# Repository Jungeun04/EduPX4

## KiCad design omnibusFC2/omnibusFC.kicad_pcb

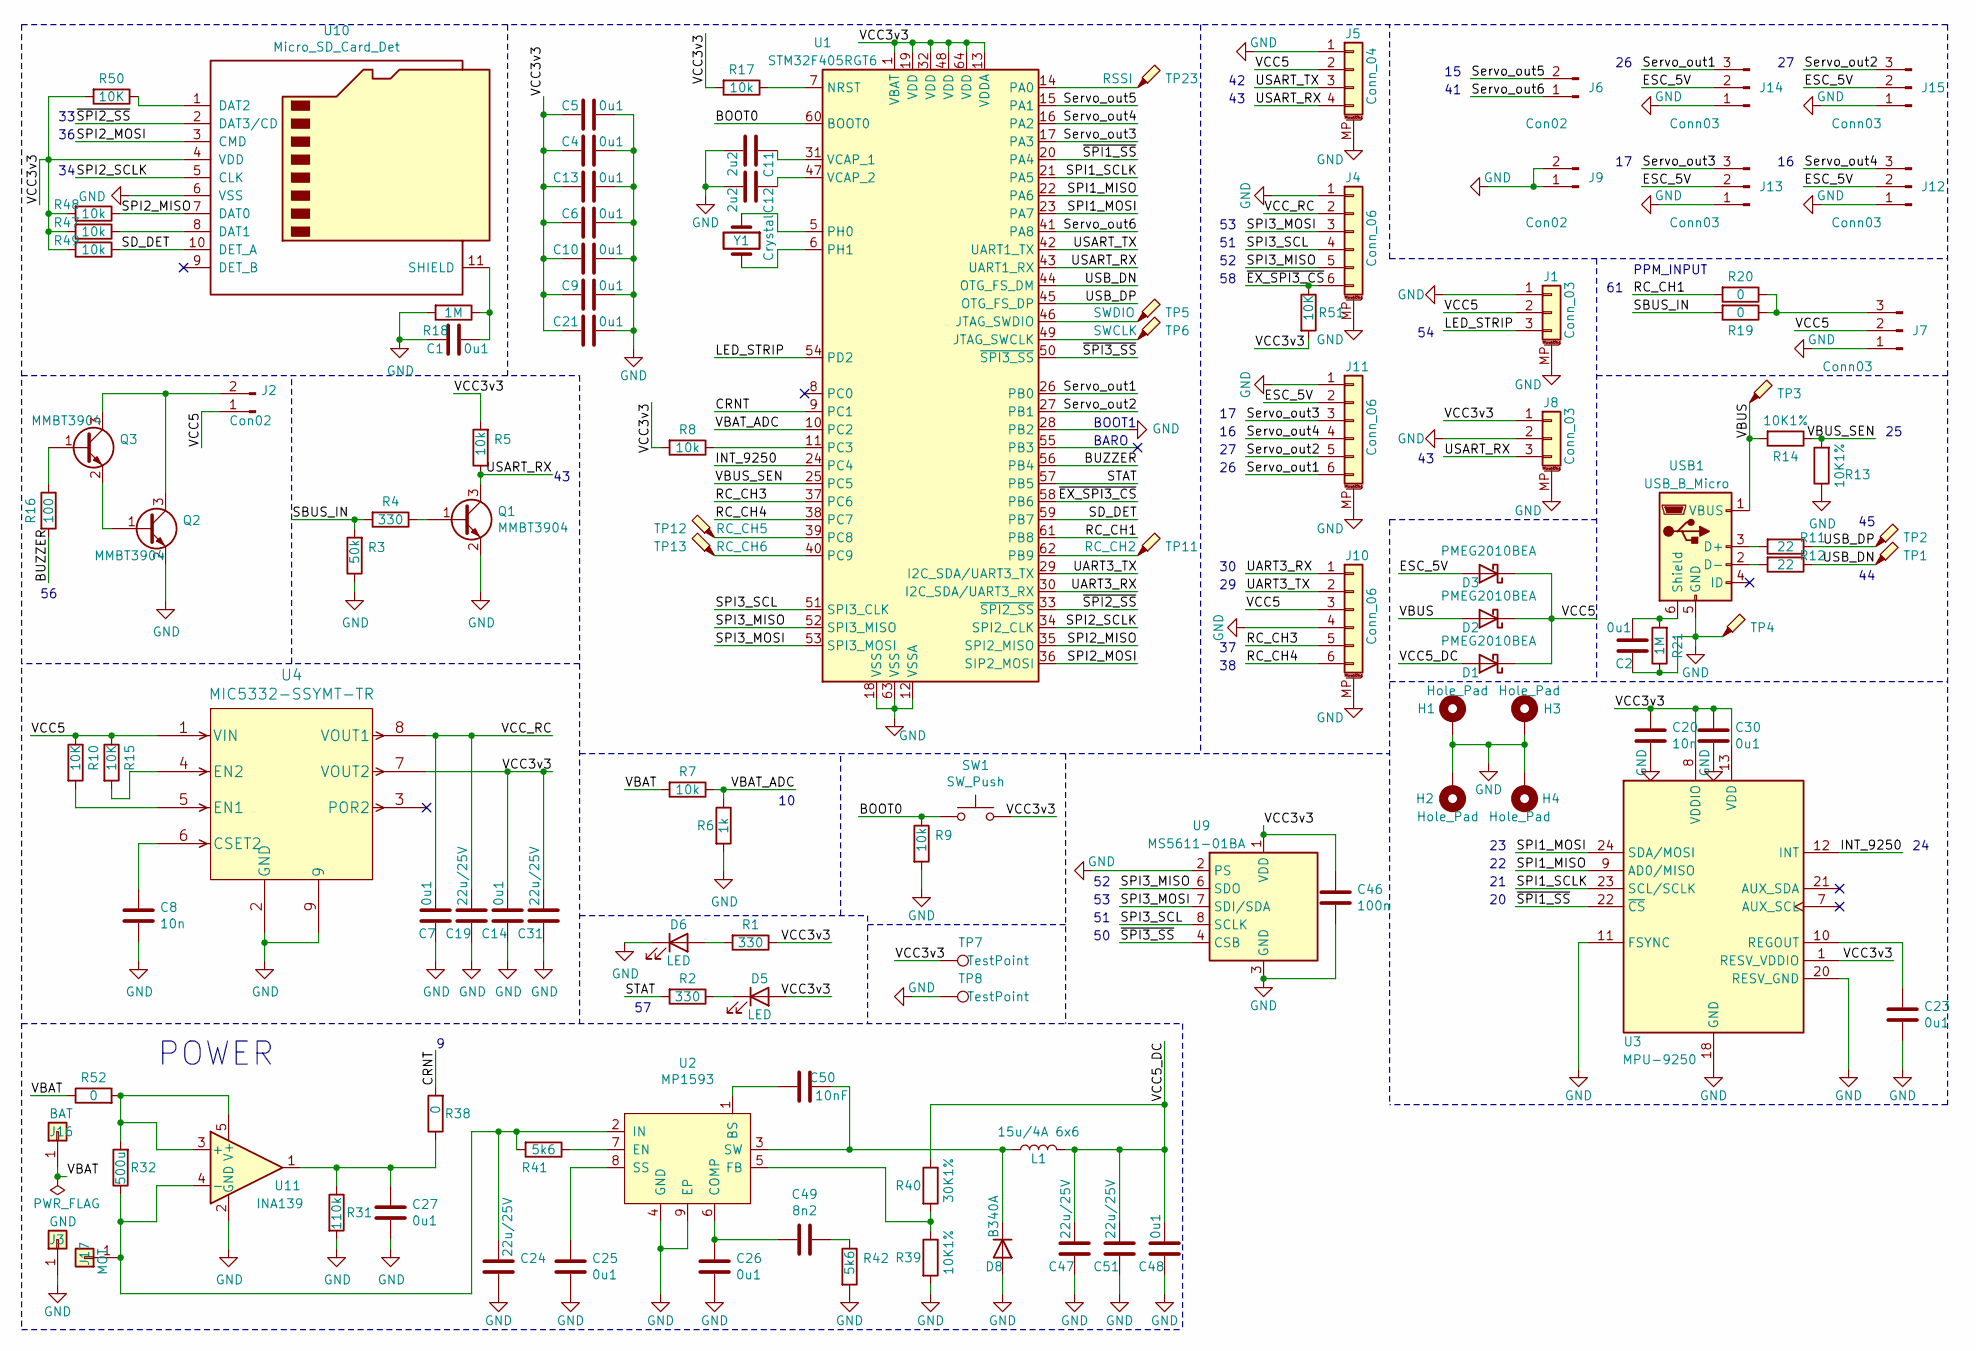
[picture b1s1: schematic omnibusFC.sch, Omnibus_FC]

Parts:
C1, C2, C4, C5, C6, C7, C9, C10, C13, C14, C21, C23, C25, C26, C27, C30, C48: 0u1; C_0402_1005Metric
C8, C20: 10n; C_0402_1005Metric
C11, C12: 2u2; C_0402_1005Metric
C19, C24, C47, C51: 22u/25V; C_0805_2012Metric
C31: 22u/25V; C_0805_2012Metric_Pad1.15x1.40mm_HandSolder
C46: 100n; C_0402_1005Metric
C49: 8n2; C_0402_1005Metric
C50: 10nF; C_0402_1005Metric
D1, D2, D3: PMEG2010BEA; D_SOD-323
D5, D6: LED; LED_0603_1608Metric_Pad1.05x0.95mm_HandSolder
D8: B340A; D_SMA
H1, H2, H3, H4: Hole_Pad; MountingHole_3mm_Pad
J1, J8: Conn_03; JST_GH_SM03B-GHS-TB_1x03-1MP_P1.25mm_Horizontal
J2, J6, J9: Con02; PinSocket_1x02_P2.54mm_Vertical
J3: GND; BAT
J4, J10, J11: Conn_06; JST_GH_SM06B-GHS-TB_1x06-1MP_P1.25mm_Horizontal
J5: Conn_04; JST_GH_SM04B-GHS-TB_1x04-1MP_P1.25mm_Horizontal
J7, J12, J13, J14, J15: Conn03; PinSocket_1x03_P2.54mm_Vertical
J16: BAT
J17: MOT; BAT
L1: 15u/4A 6x6; L_6.3x6.3_H3
Q1, Q2, Q3: MMBT3904; SOT-23
R1, R2, R4: 330; R_0402_1005Metric
R3: 50k; R_0402_1005Metric
R5, R7, R8, R9, R17, R47, R48, R49: 10k; R_0402_1005Metric
R6: 1k; R_0402_1005Metric
R10, R15, R50, R51: 10K; R_0402_1005Metric
R11, R12: 22; R_0402_1005Metric
R13, R14, R39: 10K1%; R_0402_1005Metric
R16: 100; R_0402_1005Metric
R18, R21: 1M; R_0402_1005Metric
R19, R20, R38, R52: 0; R_0402_1005Metric
R31: 110k; R_0402_1005Metric
R32: 500u; CSS2725FTL500
R40: 30K1%; R_0402_1005Metric
R41, R42: 5k6; R_0402_1005Metric
SW1: SW_Push; SW_SPST_B3U-1000P
TP1: USB_DP; TestPoint_Pad_D1.0mm
TP2: USB_DN; TestPoint_Pad_D1.0mm
TP3: VBUS; TestPoint_Pad_D1.0mm
TP4: GND; TestPoint_Pad_D1.0mm
TP5: SWDIO; TestPoint_Pad_D1.0mm
TP6: SWCLK; TestPoint_Pad_D1.0mm
TP7, TP8: TestPoint; TestPoint_Pad_D1.0mm
TP11: RC_CH2; TestPoint_Pad_D1.0mm
TP12: RC_CH5; TestPoint_Pad_D1.0mm
TP13: RC_CH6; TestPoint_Pad_D1.0mm
TP23: RSSI; TestPoint_Pad_D1.0mm
U1: STM32F405RGT6; LQFP-64_10x10mm_P0.5mm
U2: MP1593; mp1593
U3: MPU-9250; mpu9250
U4: MIC5332-SSYMT-TR; TMLF-8_MCH
U9: MS5611-01BA; LGA-8_3x5mm_P1.25mm
U10: Micro_SD_Card_Det; uSD
U11: INA139; SOT-23-5
USB1: USB_B_Micro; USB_Micro-B_Molex_47346-0001
Y1: Crystal; Resonator_SMD_muRata_CSTxExxV-3Pin_3.0x1.1mm

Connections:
/BOOT0: R9.1, SW1.1, U1.60 (BOOT0)
/BUZZER: R16.2, U1.56 (PB4)
/CRNT: R38.2, U1.9 (PC1)
/ESC_5V: D3.2 (A), J11.2, J12.2, J13.2, J14.2, J15.2
/INT_9250: U1.24 (PC4), U3.12 (INT)
/LED_STRIP: J1.3, U1.54 (PD2)
/RC_CH1: R20.2, U1.61 (PB8)
/RC_CH3: J10.5, U1.37 (PC6)
/RC_CH4: J10.6, U1.38 (PC7)
/SBUS_IN: R3.2, R4.2, R19.2
/SD_DET: R49.1, U1.59 (PB7), U10.10 (DET_A)
/SPI1_MISO: U1.22 (PA6), U3.9 (AD0/MISO)
/SPI1_MOSI: U1.23 (PA7), U3.24 (SDA/MOSI)
/SPI1_SCLK: U1.21 (PA5), U3.23 (SCL/SCLK)
/SPI2_MISO: R48.1, U1.35 (SPI2_MISO), U10.7 (DAT0)
/SPI2_MOSI: U1.36 (SIP2_MOSI), U10.3 (CMD)
/SPI2_SCLK: U1.34 (SPI2_CLK), U10.5 (CLK)
/SPI3_MISO: J4.5, U1.52 (SPI3_MISO), U9.6 (SDO)
/SPI3_MOSI: J4.3, U1.53 (SPI3_MOSI), U9.7 (SDI/SDA)
/SPI3_SCL: J4.4, U1.51 (SPI3_CLK), U9.8 (SCLK)
/STAT: R2.2, U1.57 (PB5)
/Servo_out1: J11.6, J14.3, U1.26 (PB0)
/Servo_out2: J11.5, J15.3, U1.27 (PB1)
/Servo_out3: J11.3, J13.3, U1.17 (PA3)
/Servo_out4: J11.4, J12.3, U1.16 (PA2)
/Servo_out5: J6.2, U1.15 (PA1)
/Servo_out6: J6.1, U1.41 (PA8)
/UART3_RX: J10.1, U1.30 (I2C_SDA/UART3_RX)
/UART3_TX: J10.2, U1.29 (I2C_SDA/UART3_TX)
/USART_RX: J5.4, J8.3, Q1.3 (C), R5.1, U1.43 (UART1_RX)
/USART_TX: J5.3, U1.42 (UART1_TX)
/USB_DN: R12.1, TP1.1, U1.44 (OTG_FS_DM)
/USB_DP: R11.1, TP2.1, U1.45 (OTG_FS_DP)
/VBAT: J16.1, R7.2, R52.1
/VBAT_ADC: R6.1, R7.1, U1.10 (PC2)
/VBUS: D2.2 (A), R14.2, TP3.1, USB1.1 (VBUS)
/VBUS_SEN: R13.2, R14.1, U1.25 (PC5)
/VCC3v3: C4.1, C5.1, C6.1, C9.1, C10.1, C13.1, C14.1, C20.1, C21.1, C30.1, C31.1, C46.1, D5.2 (A), J8.1, R1.1, R5.2, R8.2, R17.2, R47.2, R48.2, R49.2, R50.2, R51.2, SW1.2, TP7.1, U1.1 (VBAT), U1.13 (VDDA), U1.19 (VDD), U1.32 (VDD), U1.48 (VDD), U1.64 (VDD), U3.1 (RESV_VDDIO), U3.8 (VDDIO), U3.13 (VDD), U4.7 (VOUT2), U9.1 (VDD), U10.4 (VDD)
/VCC5: D1.1 (K), D2.1 (K), D3.1 (K), J1.2, J2.1, J5.2, J7.2, J10.3, R10.1, R15.1, U4.1 (VIN)
/VCC5_DC: C47.1, C48.1, C51.1, D1.2 (A), L1.2, R40.1
/VCC_RC: C7.1, C19.1, J4.2, U4.8 (VOUT1)
/~EX_SPI3_CS: J4.6, R51.1, U1.58 (PB6)
/~SPI1_SS: U1.20 (PA4), U3.22 (~CS)
/~SPI2_SS: U1.33 (~SPI2_SS), U10.2 (DAT3/CD)
/~SPI3_SS: U1.50 (~SPI3_SS), U9.4 (CSB), U9.5 (CSB)
GND: C1.1, C2.2, C4.2, C5.2, C6.2, C7.2, C8.2, C9.2, C10.2, C11.2, C12.2, C13.2, C14.2, C19.2, C20.2, C21.2, C23.2, C24.2, C25.2, C26.2, C27.2, C30.2, C31.2, C46.2, C47.2, C48.2, C51.2, D6.1 (K), D8.2 (A), H1.1, H2.1, H3.1, H4.1, J1.1, J1.MP (MountPin), J3.1, J4.1, J4.MP (MountPin), J5.1, J5.MP (MountPin), J7.1, J8.2, J8.MP (MountPin), J9.1, J9.2, J10.4, J10.MP (MountPin), J11.1, J11.MP (MountPin), J12.1, J13.1, J14.1, J15.1, Q1.2 (E), Q2.2 (E), R3.1, R6.2, R9.2, R13.1, R18.2, R21.1, R31.2, R39.2, R42.2, TP4.1, TP8.1, U1.12 (VSSA), U1.18 (VSS), U1.28 (PB2), U1.63 (VSS), U2.4 (GND), U2.9 (EP), U3.11 (FSYNC), U3.18 (GND), U3.20 (RESV_GND), U4.2 (GND), U4.9, U9.2 (PS), U9.3 (GND), U10.6 (VSS), U11.2 (GND), USB1.5 (GND)
unnamed: C1.2, R18.1, U10.11 (SHIELD)
unnamed: C2.1, R21.2, USB1.6 (Shield)
unnamed: C8.1, U4.6 (CSET2)
unnamed: C11.1, U1.31 (VCAP_1)
unnamed: C12.1, U1.47 (VCAP_2)
unnamed: C23.1, U3.10 (REGOUT)
unnamed: C24.1, J17.1, R32.1, R41.2, U2.2 (IN), U11.4 (-)
unnamed: C25.1, U2.8 (SS)
unnamed: C26.1, C49.2, U2.6 (COMP)
unnamed: C27.1, R31.1, R38.1, U11.1
unnamed: C49.1, R42.1
unnamed: C50.1, D8.1 (K), L1.1, U2.3 (SW)
unnamed: C50.2, U2.1 (BS)
unnamed: D5.1 (K), R2.1
unnamed: D6.2 (A), R1.2
unnamed: J2.2, Q2.3 (C), Q3.3 (C)
unnamed: J7.3, R19.1, R20.1
unnamed: Q1.1 (B), R4.1
unnamed: Q2.1 (B), Q3.2 (E)
unnamed: Q3.1 (B), R16.1
unnamed: R8.1, U1.11 (PC3)
unnamed: R10.2, U4.5 (EN1)
unnamed: R11.2, USB1.3 (D+)
unnamed: R12.2, USB1.2 (D-)
unnamed: R15.2, U4.4 (EN2)
unnamed: R17.1, U1.7 (NRST)
unnamed: R32.2, R52.2, U11.3 (+), U11.5 (V+)
unnamed: R39.1, R40.2, U2.5 (FB)
unnamed: R41.1, U2.7 (EN)
unnamed: R47.1, U10.8 (DAT1)
unnamed: R50.1, U10.1 (DAT2)
unnamed: TP5.1, U1.46 (JTAG_SWDIO)
unnamed: TP6.1, U1.49 (JTAG_SWCLK)
unnamed: TP11.1, U1.62 (PB9)
unnamed: TP12.1, U1.39 (PC8)
unnamed: TP13.1, U1.40 (PC9)
unnamed: TP23.1, U1.14 (PA0)
unnamed: U1.5 (PH0), Y1.1
unnamed: U1.6 (PH1), Y1.2

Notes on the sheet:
POWER
BOOT1
PPM_INPUT
BARO

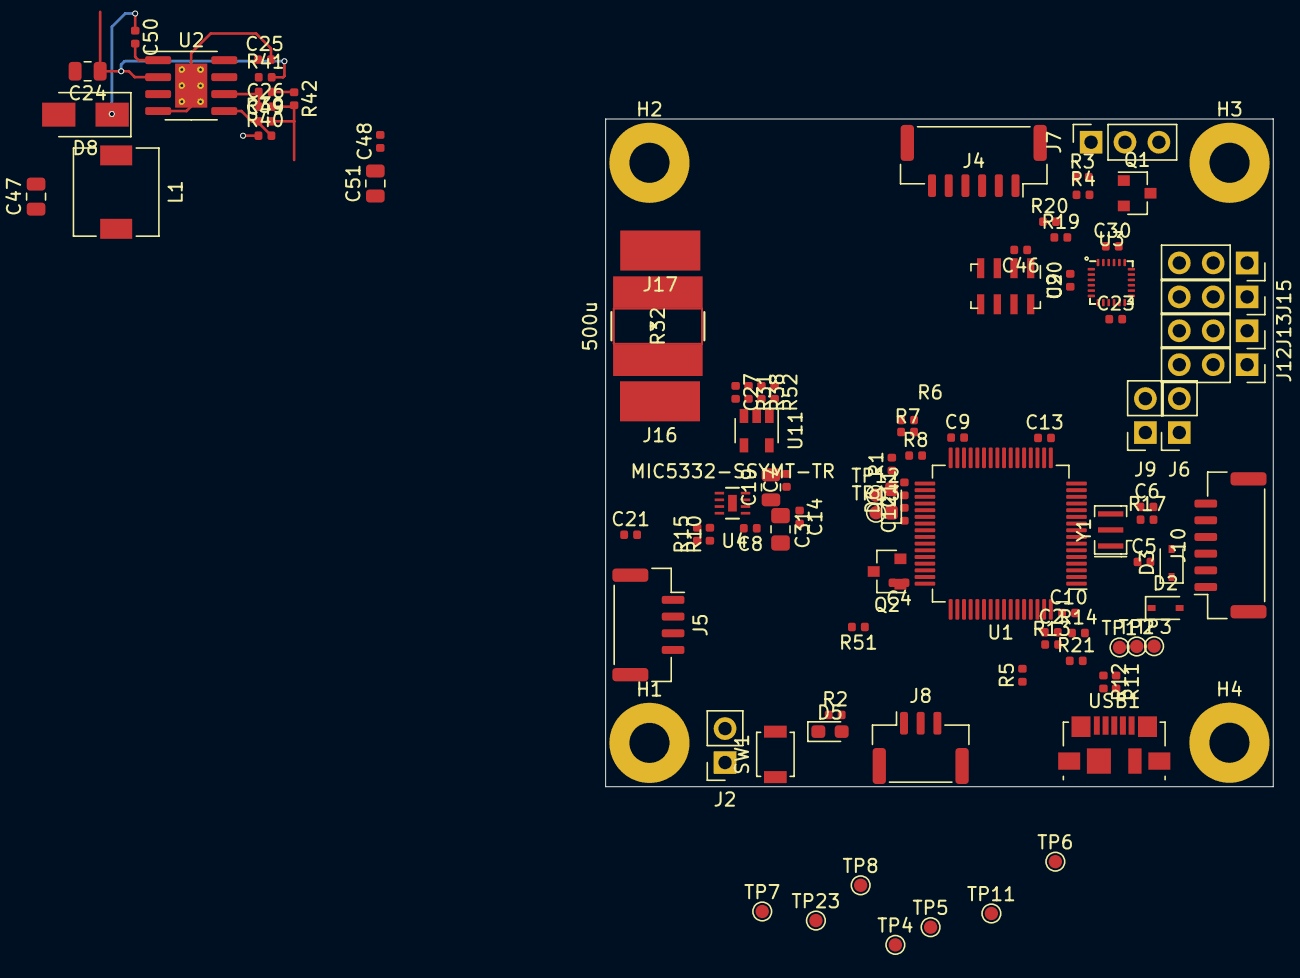
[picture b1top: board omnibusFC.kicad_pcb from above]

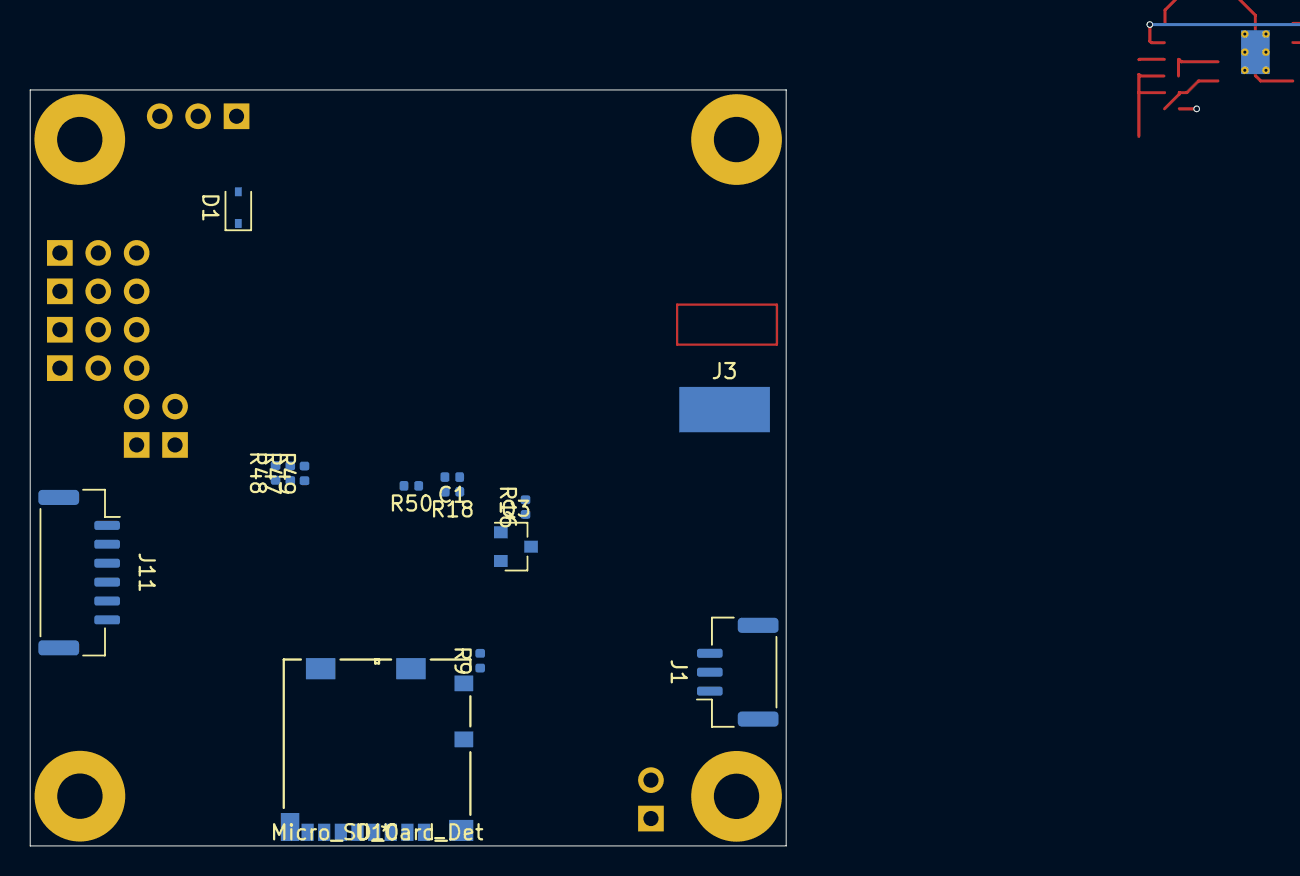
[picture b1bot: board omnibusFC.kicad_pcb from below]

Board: 4 copper layers, 50.0 x 50.0 mm, 116 parts (14 on the bottom side), 85 nets.

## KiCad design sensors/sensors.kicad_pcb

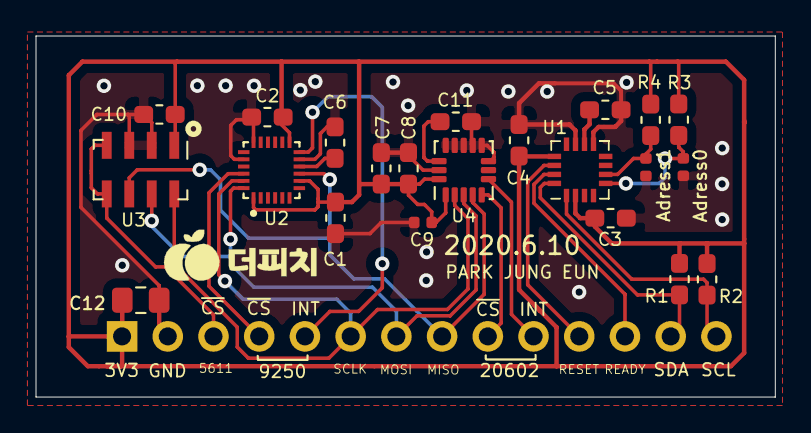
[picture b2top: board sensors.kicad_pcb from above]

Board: 2 copper layers, 41.1 x 20.1 mm, 23 parts (1 on the bottom side), 19 nets.

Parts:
Adress0, Adress1: Jumper; C_0402_1005Metric
C1: 10n/4V; C_0603_1608Metric_Pad1.05x0.95mm_HandSolder
C2: 0u1/4V; C_0603_1608Metric_Pad1.05x0.95mm_HandSolder
C3, C4, C7, C11: 0u1; C_0603_1608Metric_Pad1.05x0.95mm_HandSolder
C5: 4u7; C_0603_1608Metric_Pad1.05x0.95mm_HandSolder
C6: 0u1/2V; C_0603_1608Metric_Pad1.05x0.95mm_HandSolder
C8: 2u2; C_0603_1608Metric_Pad1.05x0.95mm_HandSolder
C9: 10n; C_0402_1005Metric
C10: 100n; C_0603_1608Metric_Pad1.05x0.95mm_HandSolder
C12: C; C_0805_2012Metric_Pad1.15x1.40mm_HandSolder
J1: Conn_01x14_Male; PinHeader_1x14_P2.54mm_Vertical
R1, R2, R3, R4: 5k1; R_0603_1608Metric_Pad1.05x0.95mm_HandSolder
U1: IST8310; LGA-16_3x3mm_P0.5mm
U2: MPU-9250; QFN40P300X300X105-24N
U3: MS5611-01BA; LGA-8_3x5mm_P1.25mm
U4: ICM-20602; LGA-16_3x3mm_P0.5mm_LayoutBorder3x5y

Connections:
GND: Adress0.2, Adress1.2, C1.2, C2.2, C3.2, C4.2, C5.2, C6.2, C7.2, C8.2, C9.2, C10.2, C11.2, C12.1, J1.2, U1.9, U1.11, U2.11, U2.18, U2.20, U3.2, U3.3, U4.8, U4.9, U4.10, U4.11, U4.12, U4.13, U4.15
INT_9250: J1.5, U2.12
INT_20602: J1.10, U4.6
MISO: J1.8, U2.9, U3.6, U4.4
MOSI: J1.7, U2.24, U3.7, U4.3
unnamed: C5.1, U1.10
unnamed: C6.1, U2.10
unnamed: C11.1, U4.14
unnamed: Adress0.1, R3.1, U1.5
unnamed: Adress1.1, R4.1, U1.6
READY: J1.12, U1.15
RESET: J1.11, U1.14
SCL: J1.14, R2.1, U1.1
SCLK: J1.6, U2.23, U3.8, U4.2
SDA: J1.13, R1.1, U1.16
VDD: C1.1, C2.1, C3.1, C4.1, C7.1, C8.1, C9.1, C10.1, C12.2, J1.1, R1.2, R2.2, R3.2, R4.2, U1.2, U1.13, U2.1, U2.8, U2.13, U3.1, U4.1, U4.16
~CS_5611: J1.3, U3.4, U3.5
~CS_9250: J1.4, U2.22
~CS_20602: J1.9, U4.5

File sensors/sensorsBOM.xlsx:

Ref | Qnty | Value | Part | manf#
C1 | 1 | 10n | Device:C
C2, C3, C4, C6, C7, C11 | 6 | 0u1 | Device:C
C5 | 1 | 4u7 | Device:C
C8 | 1 | 2u2 | Device:C
C9 | 1 | 10n | Device:C
C10 | 1 | 100n | Device:C
C12, C13 | 2 | 22uF | Device:C
J1 | 1 | Conn_01x14_Male | Connector:Conn_01x14_Male
R1, R2, R3, R4 | 4 | 5k1 | Device:R
U1 | 1 | IST8310 | Sensor_Magnetic:IST8310 | ~
U2 | 1 | MPU-9250 | Sensor_Motion:MPU-9250 | ~
U3 | 1 | MS5611-01BA | Sensor_Pressure:MS5611-01BA
U4 | 1 | ICM-20602 | Sensor_Motion:ICM-20602
 | 22

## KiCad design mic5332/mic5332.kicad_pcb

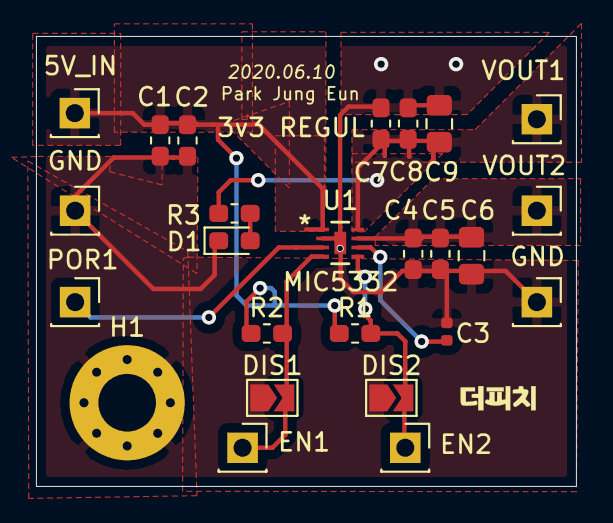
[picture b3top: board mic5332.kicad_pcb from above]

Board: 2 copper layers, 30.0 x 25.0 mm, 25 parts (0 on the bottom side), 9 nets.

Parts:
5V_IN: 5V_IN; Socket_1x01_P2.54mm_Vertical
C1, C5, C8: 0u1; C_0603_1608Metric_Pad1.05x0.95mm_HandSolder
C2: 10u/25v; C_0603_1608Metric_Pad1.05x0.95mm_HandSolder
C3: 10n; C_0402_1005Metric
C4, C7: 1u; C_0603_1608Metric_Pad1.05x0.95mm_HandSolder
C6, C9: 22u/25V; C_0805_2012Metric_Pad1.15x1.40mm_HandSolder
D1: RED_LED; LED_0603_1608Metric_Pad1.05x0.95mm_HandSolder
DIS1, DIS2: Jumper_2_Open; SolderJumper-2_P1.3mm_Open_TrianglePad1.0x1.5mm
EN1: EN2; Socket_1x01_P2.54mm_Vertical
EN2: EN1; Socket_1x01_P2.54mm_Vertical
GND: GND; Socket_1x01_P2.54mm_Vertical
GND#2: GND; Socket_1x01_P2.54mm_Vertical
H1: MountingHole_Pad; MountingHole_3.2mm_M3_Pad_Via
POR1: POR2; Socket_1x01_P2.54mm_Vertical
R1, R2: 10K; R_0603_1608Metric_Pad1.05x0.95mm_HandSolder
R3: 330; R_0603_1608Metric_Pad1.05x0.95mm_HandSolder
U1: MIC5332; TMLF-8_MCH
VOUT1: VOUT1; Socket_1x01_P2.54mm_Vertical
VOUT2: VOUT2; Socket_1x01_P2.54mm_Vertical

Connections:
GND: C1.2, C2.2, C3.2, C4.2, C5.2, C6.2, C7.2, C8.2, C9.2, D1.1, DIS1.1, DIS2.1, GND.1, GND#2.1, H1.1, U1.2, U1.9
unnamed: 5V_IN.1, C1.1, C2.1, R1.1, R2.1, U1.1
unnamed: C3.1, U1.6
unnamed: C4.1, C5.1, C6.1, U1.7, VOUT2.1
unnamed: C7.1, C8.1, C9.1, R3.1, U1.8, VOUT1.1
unnamed: D1.2, R3.2
unnamed: DIS1.2, EN1.1, R2.2, U1.4
unnamed: DIS2.2, EN2.1, R1.2, U1.5
unnamed: POR1.1, U1.3

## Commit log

2020-05-21 처음만든것
2020-05-21 Kicad
    첫 파일
2020-05-25 2번
    사진추가
2020-05-26 5월26일 수정
    BOM파일 추가, 사진추가
2020-06-01 kk.md
    4
2020-06-01 6월1일
    수정
2020-06-08 6월8일
2020-06-09 6월9일
2020-06-16 6월16일
2020-07-20 보드크기변경
    그리기 어려워서 Multiwii_lite크기로 변경

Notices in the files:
parts and their libraries:
Copyright 2016 Accelerated Designs. All rights reserved.
